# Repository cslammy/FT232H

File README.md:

# FT232H
Python and Arduino code to get started with FT232H FTDI Breakout Boards.

This is code that accompanies these AUDIODIWHY blog posts:
http://audiodiwhy.blogspot.com/2020/12/ftdi232h-breakout-board-affordable-usb.html
http://audiodiwhy.blogspot.com/2020/12/ftdi232h-breakout-board-affordable-usb.html

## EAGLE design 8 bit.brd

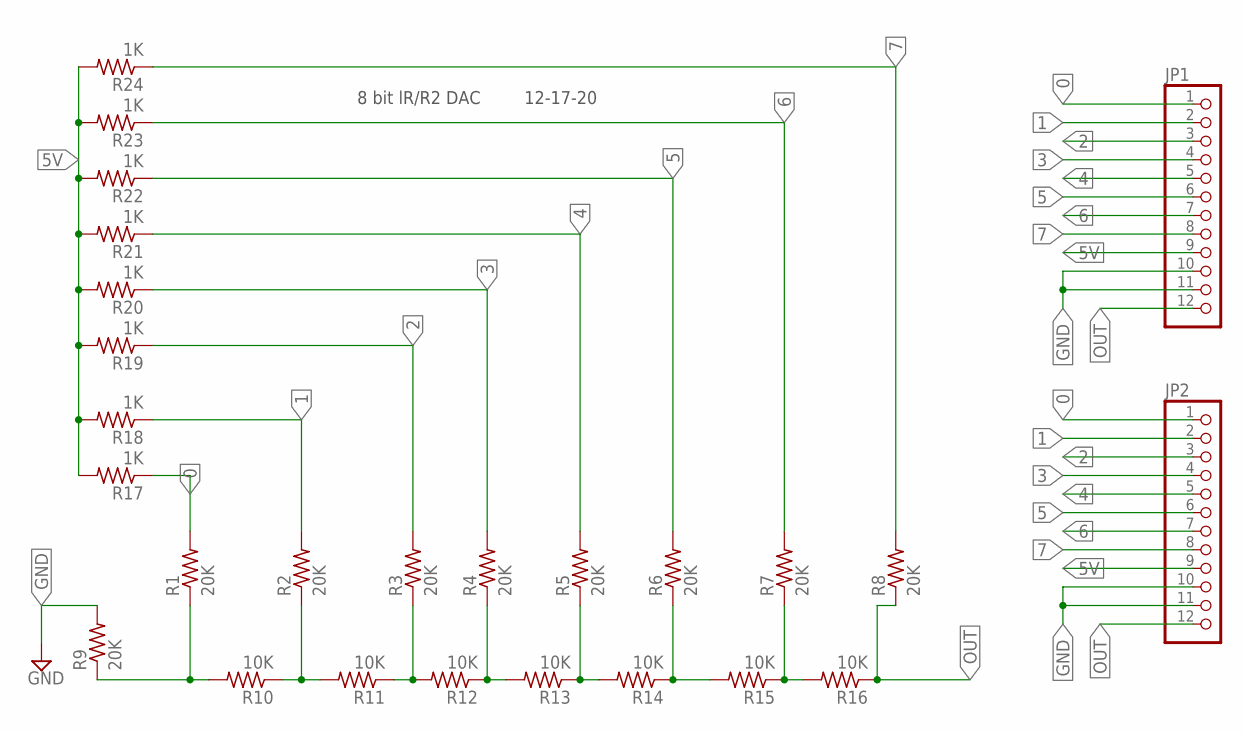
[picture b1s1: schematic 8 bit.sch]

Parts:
JP1, JP2: PINHD-1X12; 1X12
R1, R2, R3, R4, R5, R6, R7, R8, R9: 20K; 0204/7
R10, R11, R12, R13, R14, R15, R16: 10K; 0204/7
R17, R18, R19, R20, R21, R22, R23, R24: 1K; 0204/7

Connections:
0: JP1.1, JP2.1, R1.2, R17.1
1: JP1.2, JP2.2, R2.2, R18.1
2: JP1.3, JP2.3, R3.2, R19.1
3: JP1.4, JP2.4, R4.2, R20.1
4: JP1.5, JP2.5, R5.2, R21.1
5: JP1.6, JP2.6, R6.2, R22.1
5V: JP1.9, JP2.9, R17.2, R18.2, R19.2, R20.2, R21.2, R22.2, R23.2, R24.2
6: JP1.7, JP2.7, R7.2, R23.1
7: JP1.8, JP2.8, R8.2, R24.1
GND: JP1.10, JP1.11, JP2.10, JP2.11, R9.2
unnamed: R1.1, R9.1, R10.2
unnamed: R2.1, R10.1, R11.2
unnamed: R3.1, R11.1, R12.2
unnamed: R4.1, R12.1, R13.2
unnamed: R5.1, R13.1, R14.2
unnamed: R6.1, R14.1, R15.2
unnamed: R7.1, R15.1, R16.2
OUT: JP1.12, JP2.12, R8.1, R16.1

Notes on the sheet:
8 bit lR/R2 DAC
12-17-20

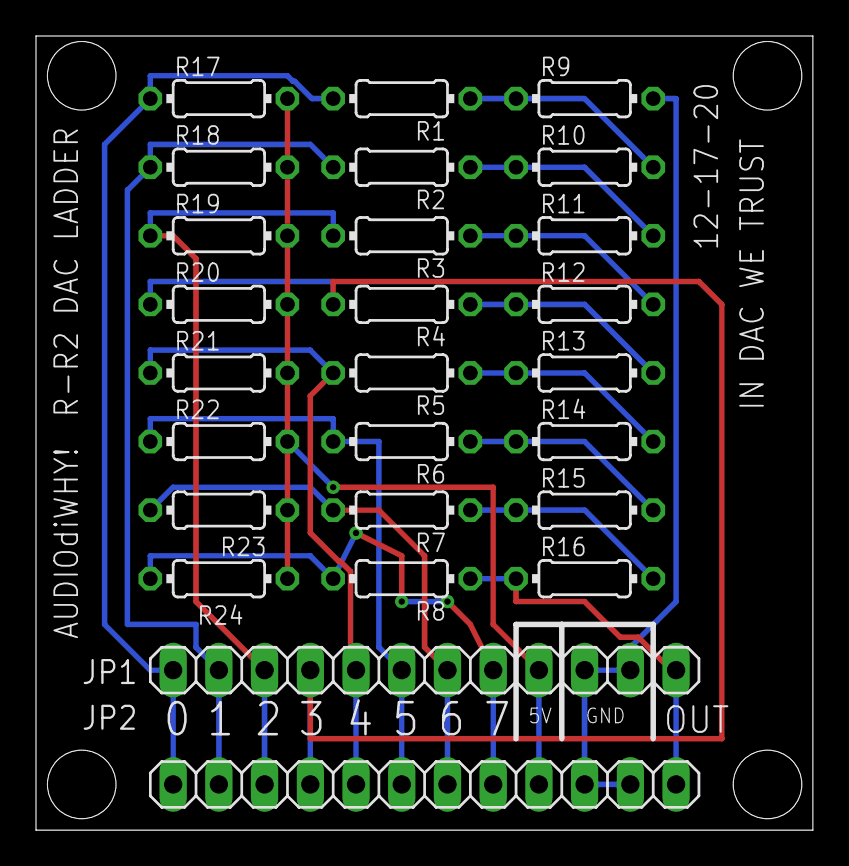
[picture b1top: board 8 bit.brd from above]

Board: 2 copper layers, 43.2 x 44.1 mm, 26 parts (0 on the bottom side), 18 nets.

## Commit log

2020-12-23 Update README.md
    Python and Arduino code to get started with FT232H FTDI Breakout Boards.
    This is code that accompanies these AUDIODIWHY blog posts:
    http://audiodiwhy.blogspot.com/2020/12/ftdi232h-breakout-board-affordable-usb.html
    http://audiodiwhy.blogspot.com/2020/12/ftdi232h-breakout-board-affordable-usb.html
2021-01-02 Eagle 8 bit DAC
2021-03-11 Added 3 new ICs mcp3008 mcp4922 max9939
    See this blog post for more info. I will add more IC shakeout PYFTDI files as I test them working. http://audiodiwhy.blogspot.com/2020/12/ftdi232h-breakout-board-affordable-usb.html http://audiodiwhy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
